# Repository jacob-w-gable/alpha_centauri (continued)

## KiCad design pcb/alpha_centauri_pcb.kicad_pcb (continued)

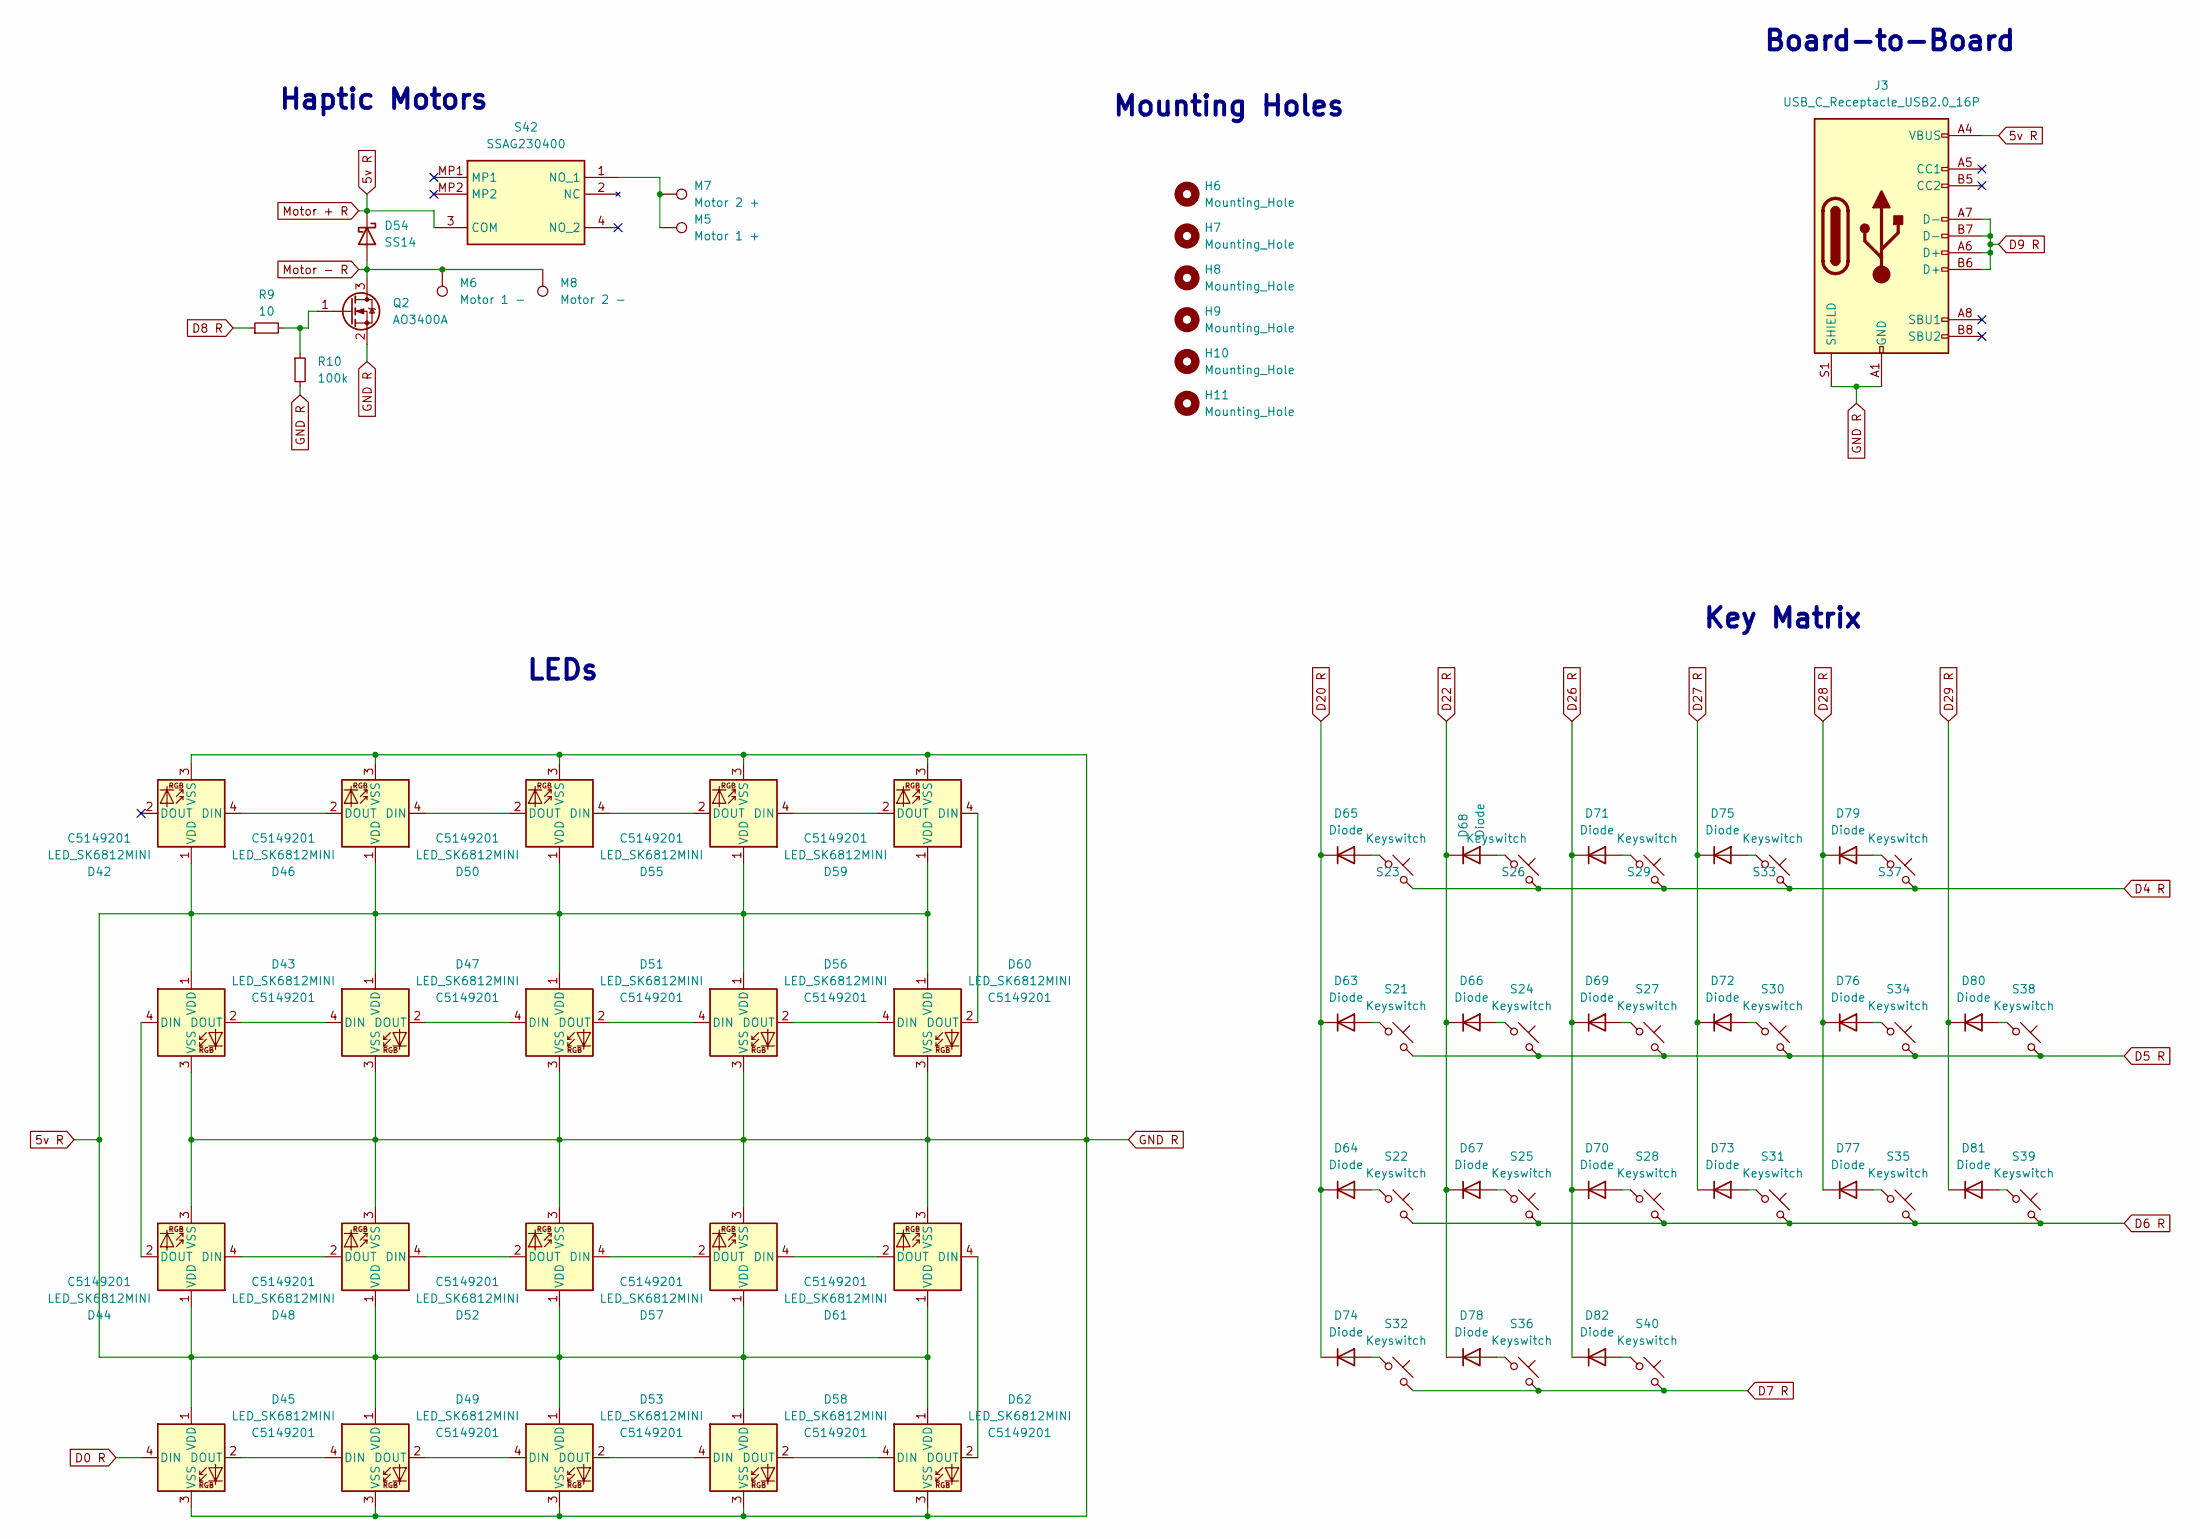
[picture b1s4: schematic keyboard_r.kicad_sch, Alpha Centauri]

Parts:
D42, D43, D44, D45, D46, D47, D48, D49, D50, D51, D52, D53, D55, D56, D57, D58, D59, D60, D61, D62: LED_SK6812MINI; LCSC C5149201
D54: SS14; D_SMA
D63, D64, D65, D66, D67, D68, D69, D70, D71, D72, D73, D74, D75, D76, D77, D78, D79, D80, D81, D82: Diode; Diode_SOD-123
H6, H7, H8, H9, H10, H11: Mounting_Hole; MountingHole_4.3mm_M4
J3: USB_C_Receptacle_USB2.0_16P; USB_C_Receptacle_HRO_TYPE-C-31-M-12
M5: Motor 1 +; TestPoint_Pad_2.5x2.5mm
M6: Motor 1 -; TestPoint_Pad_2.5x2.5mm
M7: Motor 2 +; TestPoint_Pad_2.5x2.5mm
M8: Motor 2 -; TestPoint_Pad_2.5x2.5mm
Q2: AO3400A; SOT-23
R9: 10; R_0603_1608Metric
R10: 100k; R_0603_1608Metric
S21, S22, S23, S24, S25, S26, S27, S28, S29, S30, S31, S32, S33, S34, S35, S36, S37, S39, S40: Keyswitch; MX_Choc_Hotswap_Hybrid
S38: Keyswitch; MX_Choc_Hotswap_Hybrid_1.5u
S42: SSAG230400; Manufacturer_Part_Number SSAG230400; Mouser Part Number 688-SSAG230400

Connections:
5v R: D42.1 (VDD), D43.1 (VDD), D44.1 (VDD), D45.1 (VDD), D46.1 (VDD), D47.1 (VDD), D48.1 (VDD), D49.1 (VDD), D50.1 (VDD), D51.1 (VDD), D52.1 (VDD), D53.1 (VDD), D54.1 (K), D55.1 (VDD), D56.1 (VDD), D57.1 (VDD), D58.1 (VDD), D59.1 (VDD), D60.1 (VDD), D61.1 (VDD), D62.1 (VDD), J3.A4 (VBUS), J3.A9 (VBUS), J3.B4 (VBUS), J3.B9 (VBUS), S42.3 (COM); also elsewhere on the board
D0 R: D45.4 (DIN); also elsewhere on the board
D4 R: S23.2, S26.2, S29.2, S33.2, S37.2; also elsewhere on the board
D5 R: S21.2, S24.2, S27.2, S30.2, S34.2, S38.2; also elsewhere on the board
D6 R: S22.2, S25.2, S28.2, S31.2, S35.2, S39.2; also elsewhere on the board
D7 R: S32.2, S36.2, S40.2; also elsewhere on the board
D8 R: R9.1; also elsewhere on the board
D9 R: J3.A6 (D+), J3.A7 (D-), J3.B6 (D+), J3.B7 (D-); also elsewhere on the board
D20 R: D63.1 (K), D64.1 (K), D65.1 (K), D74.1 (K); also elsewhere on the board
D22 R: D66.1 (K), D67.1 (K), D68.1 (K), D78.1 (K); also elsewhere on the board
D26 R: D69.1 (K), D70.1 (K), D71.1 (K), D82.1 (K); also elsewhere on the board
D27 R: D72.1 (K), D73.1 (K), D75.1 (K); also elsewhere on the board
D28 R: D76.1 (K), D77.1 (K), D79.1 (K); also elsewhere on the board
D29 R: D80.1 (K), D81.1 (K); also elsewhere on the board
GND R: D42.3 (VSS), D43.3 (VSS), D44.3 (VSS), D45.3 (VSS), D46.3 (VSS), D47.3 (VSS), D48.3 (VSS), D49.3 (VSS), D50.3 (VSS), D51.3 (VSS), D52.3 (VSS), D53.3 (VSS), D55.3 (VSS), D56.3 (VSS), D57.3 (VSS), D58.3 (VSS), D59.3 (VSS), D60.3 (VSS), D61.3 (VSS), D62.3 (VSS), J3.A1 (GND), J3.A12 (GND), J3.B1 (GND), J3.B12 (GND), J3.S1 (SHIELD), Q2.2 (S), R10.2; also elsewhere on the board
Motor - R: D54.2 (A), M6.1 (1_1), M8.1 (1_1), Q2.3 (D)
unnamed: D42.4 (DIN), D46.2 (DOUT)
unnamed: D43.4 (DIN), D44.2 (DOUT)
unnamed: D43.2 (DOUT), D47.4 (DIN)
unnamed: D44.4 (DIN), D48.2 (DOUT)
unnamed: D45.2 (DOUT), D49.4 (DIN)
unnamed: D46.4 (DIN), D50.2 (DOUT)
unnamed: D47.2 (DOUT), D51.4 (DIN)
unnamed: D48.4 (DIN), D52.2 (DOUT)
unnamed: D49.2 (DOUT), D53.4 (DIN)
unnamed: D50.4 (DIN), D55.2 (DOUT)
unnamed: D51.2 (DOUT), D56.4 (DIN)
unnamed: D52.4 (DIN), D57.2 (DOUT)
unnamed: D53.2 (DOUT), D58.4 (DIN)
unnamed: D55.4 (DIN), D59.2 (DOUT)
unnamed: D56.2 (DOUT), D60.4 (DIN)
unnamed: D57.4 (DIN), D61.2 (DOUT)
unnamed: D58.2 (DOUT), D62.4 (DIN)
unnamed: D59.4 (DIN), D60.2 (DOUT)
unnamed: D61.4 (DIN), D62.2 (DOUT)
unnamed: D63.2 (A), S21.1
unnamed: D64.2 (A), S22.1
unnamed: D65.2 (A), S23.1
unnamed: D66.2 (A), S24.1
unnamed: D67.2 (A), S25.1
unnamed: D68.2 (A), S26.1
unnamed: D69.2 (A), S27.1
unnamed: D70.2 (A), S28.1
unnamed: D71.2 (A), S29.1
unnamed: D72.2 (A), S30.1
unnamed: D73.2 (A), S31.1
unnamed: D74.2 (A), S32.1
unnamed: D75.2 (A), S33.1
unnamed: D76.2 (A), S34.1
unnamed: D77.2 (A), S35.1
unnamed: D78.2 (A), S36.1
unnamed: D79.2 (A), S37.1
unnamed: D80.2 (A), S38.1
unnamed: D81.2 (A), S39.1
unnamed: D82.2 (A), S40.1
unnamed: Q2.1 (G), R9.2, R10.1
unnamed: M5.1 (1_1), M7.1 (1_1), S42.1 (NO_1)

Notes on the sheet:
LEDs
Haptic Motors
Board-to-Board
Mounting Holes
Key Matrix

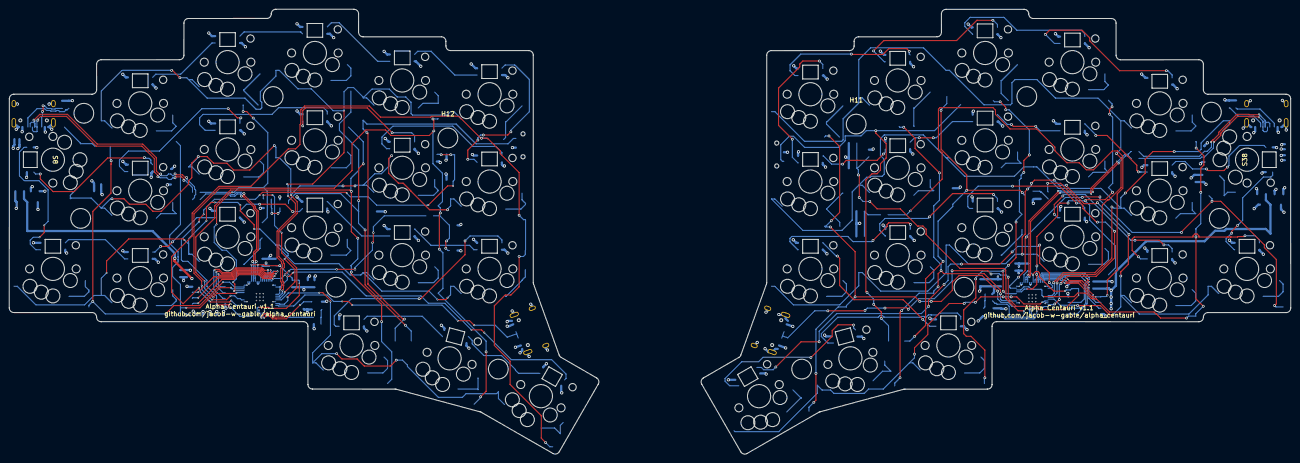
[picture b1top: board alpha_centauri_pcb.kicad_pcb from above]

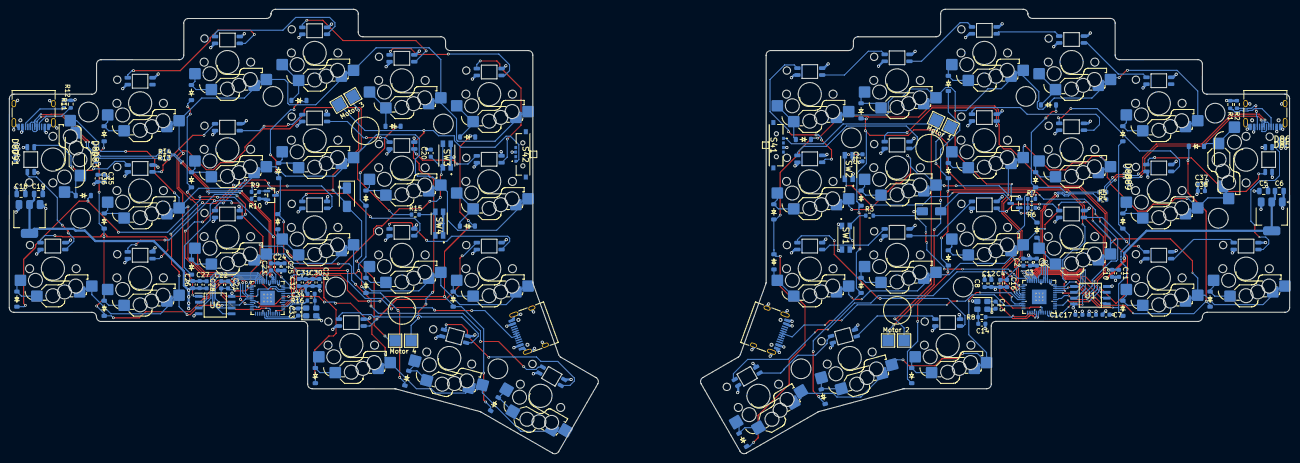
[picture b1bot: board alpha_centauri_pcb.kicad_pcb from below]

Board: 4 copper layers, 279.5 x 97.0 mm, 224 parts (172 on the bottom side), 152 nets.

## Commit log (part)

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2024-11-18 Include .gitignore
2025-01-13 More docs on the keymap design
2025-03-01 Fix #6, layer shift timing issue
2025-03-01 Bit of cleanup
2025-03-01 No need for docs/ now, since there is a Wiki
2025-03-01 Create LICENSE
2025-03-04 Pipeline test
2025-03-04 Make sure pipeline starts on create tag
2025-03-04 Try to push tags
2025-03-04 Permissions changes for workflow
2025-03-04 Use personal access token for workflow
2025-03-04 Another env variable test
2025-03-04 And another env test...
2025-03-04 Better token?
2025-03-04 Maybe now?
2025-03-04 More monolithic CI
2025-03-04 Fix outputs
2025-03-04 Fix git checkout problem in CI
2025-03-04 A tested workflow
2025-03-05 Pipeline dependency build
2025-03-08 Add pipeline
    Skip release if tag already exists
    Make sure to fetch tags
    Add Quickstart link to README.md
2025-04-07 Document layout and RGB layout in keyboard.json
2025-04-07 Fix keyboard.json JSON syntax
2025-04-15 Configure led count
2025-04-15 Remove annoying and unused emojis on cursor control layer, change ctrl timing, add meta on cursor control layer
2025-04-15 Update roadmap in README
2025-04-21 v0.1.0 release, full RGB support, case STLs
    Fully-tested firmware with RGB support
    Added STL's for the case
    Updated the roadmap
    This concludes v0.1.0 release
2025-04-21 No longer pre-release
2025-04-21 Typo in stl readme
2025-04-22 Update roadmap, since haptic feedback is technically already supported
2025-04-24 Add reset keys to keymap, fix gaming layer for 40-key layout
2025-04-24 Make the string "= " easier to type, ignoring Hold on Other Key Press
2025-04-24 Audo mount rp2040
    Script to mount rp2040
2025-04-24 Include all RGB matrix effects
    Mark mod keys in keyboard.json
2025-04-24 Version bump
2025-10-04 Update qmk_firmware
2025-10-04 Conditional colemak enable
2025-10-04 Add make recipes to flash one side at a time
2025-10-04 Use generic rp2040 MCU rather than atmega32u4
    atmega32u4 will not be supported from here on out
    Fix json parse error
2025-11-11 Experimental HID control (RGB for now)
2025-11-20 v1.0.0 initial release, with pcb files
2025-12-21 Update README's
